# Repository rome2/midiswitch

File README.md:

# RoMe Zimpel MIDI

This is a simple 3 button MIDI footswitch. It was designed to replace the huge original footswitch of my Marshall 6100LM with a smaller alternative. I've used the Digitech FS3X as base for the project as it's very cheap, sturdy and already comes with three latching footswitches. Drilling three holes for the LEDs and one for the MIDI socket makes it a great MIDI pedal.

The microcontroller used was the ATMEGA8 just because I had several of them flying around. It has a lot free IOs so the board could easily be extended with extra functionality (expression pedal, more buttons etc)

The schematic and board were created with KiCad, the code uses the default GNU toolchain for Atmel and avrdude. There are a gazillion websites out there that describe how to set this up on different operating systems so I will not go into depth here.

You might have to adjust the programmer (AVRDUDE_PROGRAMMER) and port (AVRDUDE_PORT) in the makefile to make the upload work on your system.

Usually a simple 'make all' in the code folder will be enough to build the binary. A 'make program' should upload the file to your Atmel.

The code itself is very minimalistic. Every button click creates a message on the serial port and turns the LED on.

My first attempt/prototype used a MSP430 but this was not really a good choice. The processor itself did fine but there were a lot of problems with the 3V logic and several MIDI devices. So i created the circuit again with a 5V processor and this worked much better in the end and was much simpler too.

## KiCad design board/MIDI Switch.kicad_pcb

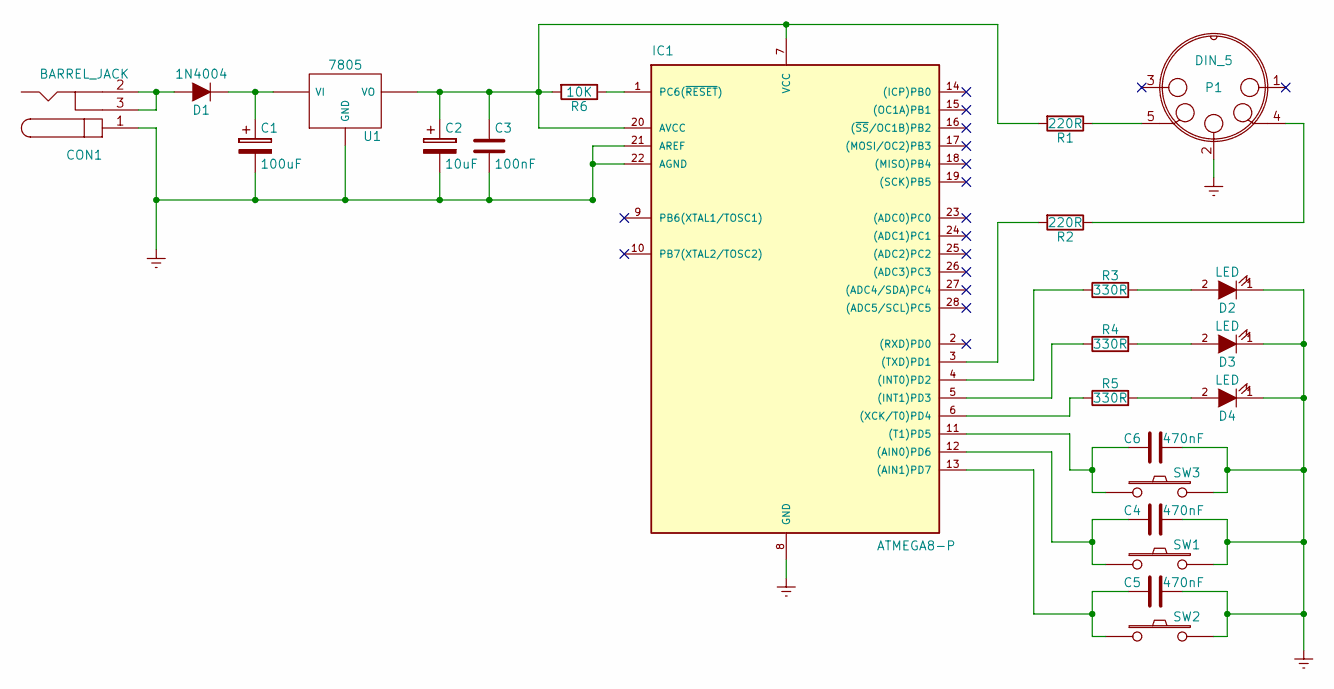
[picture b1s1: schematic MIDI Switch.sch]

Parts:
C1: 100uF; C_Radial_D8_L13_P3.8
C2: 10uF; C_Radial_D5_L11_P2.5
C3: 100nF; C_Disc_D6_P5
C4, C5, C6: 470nF; C_Disc_D6_P5
CON1: BARREL_JACK
D1: 1N4004; Diode_DO-41_SOD81_Horizontal_RM10
D2, D3, D4: LED; LED-5MM
IC1: ATMEGA8-P; DIP-28_W7.62mm
P1: DIN_5; Pin_Header_Straight_1x05
R1, R2: 220R; Resistor_Horizontal_RM10mm
R3, R4, R5: 330R; Resistor_Horizontal_RM10mm
R6: 10K; Resistor_Horizontal_RM10mm
SW1, SW2, SW3: SW_PUSH
U1: 7805; TO-220

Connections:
GNDREF: C1.2, C2.2, C3.2, C4.2, C5.2, C6.2, CON1.1, D2.1 (K), D3.1 (K), D4.1 (K), IC1.8 (GND), IC1.21 (AREF), IC1.22 (AGND), P1.2, SW1.2, SW2.2, SW3.2, U1.3 (GND)
unnamed: C1.1, D1.1 (K), U1.1 (VI)
unnamed: C2.1, C3.1, IC1.7 (VCC), IC1.20 (AVCC), R1.2, R6.2, U1.2 (VO)
unnamed: C4.1, IC1.12 ((AIN0)PD6), SW1.1
unnamed: C5.1, IC1.13 ((AIN1)PD7), SW2.1
unnamed: C6.1, IC1.11 ((T1)PD5), SW3.1
unnamed: CON1.2, CON1.3, D1.2 (A)
unnamed: D2.2 (A), R3.2
unnamed: D3.2 (A), R4.2
unnamed: D4.2 (A), R5.2
unnamed: IC1.1 (PC6(~RESET~)), R6.1
unnamed: IC1.3 ((TXD)PD1), R2.2
unnamed: IC1.4 ((INT0)PD2), R3.1
unnamed: IC1.5 ((INT1)PD3), R4.1
unnamed: IC1.6 ((XCK/T0)PD4), R5.1
unnamed: P1.4, R2.1
unnamed: P1.5, R1.1

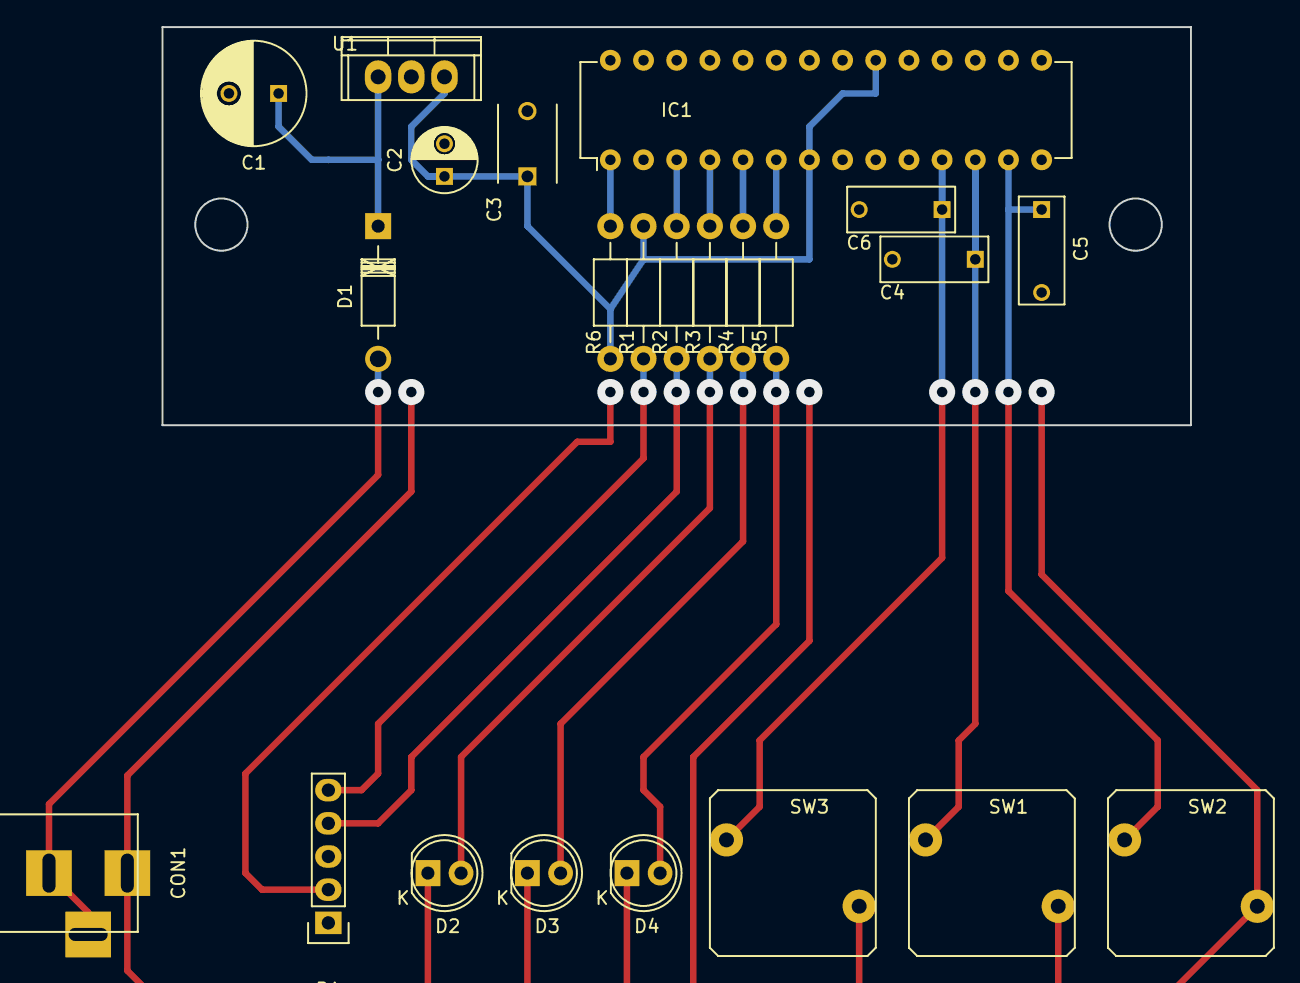
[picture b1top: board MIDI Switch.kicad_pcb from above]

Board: 2 copper layers, 23 parts (0 on the bottom side), 17 nets.

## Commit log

2016-09-18 Initial setup
2017-02-20 Added print layout
2017-02-22 Swapped button and led order
2017-02-24 Set theme jekyll-theme-slate
